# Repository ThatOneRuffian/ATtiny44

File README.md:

# ATtiny44
Messing with ATtiny44 MCU.

Making a multi-colored LED driver/controller.

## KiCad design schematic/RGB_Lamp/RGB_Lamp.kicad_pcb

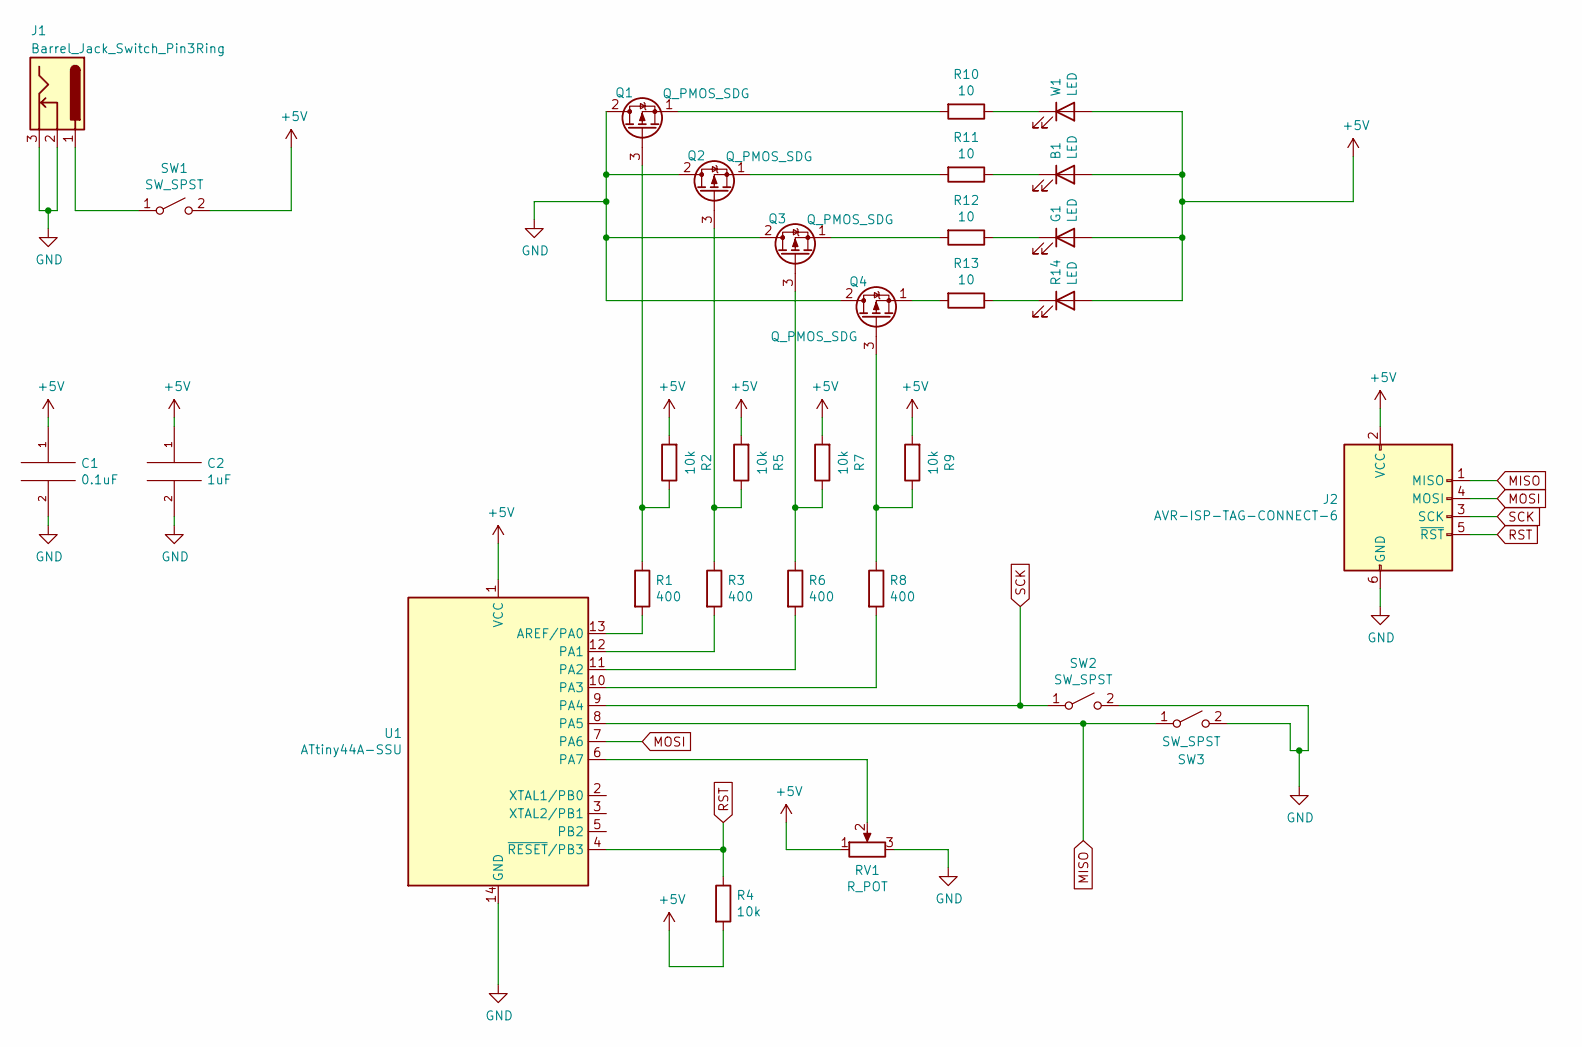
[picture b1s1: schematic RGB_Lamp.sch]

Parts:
B1: LED; PinHeader_1x02_P2.54mm_Vertical
C1: 0.1uF; C_Rect_L4.0mm_W2.5mm_P2.50mm
C2: 1uF; CP_Radial_D4.0mm_P1.50mm
G1: LED; PinHeader_1x02_P2.54mm_Vertical
J1: Barrel_Jack_Switch_Pin3Ring; BarrelJack_Horizontal
J2: AVR-ISP-TAG-CONNECT-6; TC2030-IDC-NL-10
Q1, Q2, Q3, Q4: Q_PMOS_SDG; SuperSOT-3
R1, R3, R6, R8: 400; R_Axial_DIN0207_L6.3mm_D2.5mm_P10.16mm_Horizontal
R2, R4, R5, R7, R9: 10k; R_Axial_DIN0207_L6.3mm_D2.5mm_P10.16mm_Horizontal
R10, R11, R12, R13: 10; R_Axial_DIN0207_L6.3mm_D2.5mm_P10.16mm_Horizontal
R14: LED; PinHeader_1x02_P2.54mm_Vertical
RV1: R_POT; Potentiometer_Omeg_PC16BU_Horizontal
SW1: SW_SPST; PinHeader_1x02_P2.54mm_Vertical
SW2, SW3: SW_SPST; SW_Tactile_SPST_Angled_PTS645Vx31-2LFS
U1: ATtiny44A-SSU; SOIC-14_3.9x8.7mm_P1.27mm
W1: LED; PinHeader_1x02_P2.54mm_Vertical

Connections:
+5V: B1.2 (A), C1.1, C2.1, G1.2 (A), J2.2 (VCC), R2.2, R4.2, R5.2, R7.2, R9.2, R14.2 (A), RV1.1, SW1.2 (B), U1.1 (VCC), W1.2 (A)
GND: C1.2, C2.2, J1.2, J1.3, J2.6 (GND), Q1.2 (D), Q2.2 (D), Q3.2 (D), Q4.2 (D), RV1.3, SW2.2 (B), SW3.2 (B), U1.14 (GND)
MISO: J2.1 (MISO), SW3.1 (A), U1.8 (PA5)
MOSI: J2.4 (MOSI), U1.7 (PA6)
unnamed: B1.1 (K), R11.1
unnamed: G1.1 (K), R12.1
unnamed: J1.1, SW1.1 (A)
unnamed: Q1.1 (S), R10.2
unnamed: Q1.3 (G), R1.1, R2.1
unnamed: Q2.1 (S), R11.2
unnamed: Q2.3 (G), R3.1, R5.1
unnamed: Q3.1 (S), R12.2
unnamed: Q3.3 (G), R6.1, R7.1
unnamed: Q4.1 (S), R13.2
unnamed: Q4.3 (G), R8.1, R9.1
unnamed: R1.2, U1.13 (AREF/PA0)
unnamed: R3.2, U1.12 (PA1)
unnamed: R6.2, U1.11 (PA2)
unnamed: R8.2, U1.10 (PA3)
unnamed: R10.1, W1.1 (K)
unnamed: R13.1, R14.1 (K)
unnamed: RV1.2, U1.6 (PA7)
RST: J2.5 (~RST), R4.1, U1.4 (~RESET~/PB3)
SCK: J2.3 (SCK), SW2.1 (A), U1.9 (PA4)

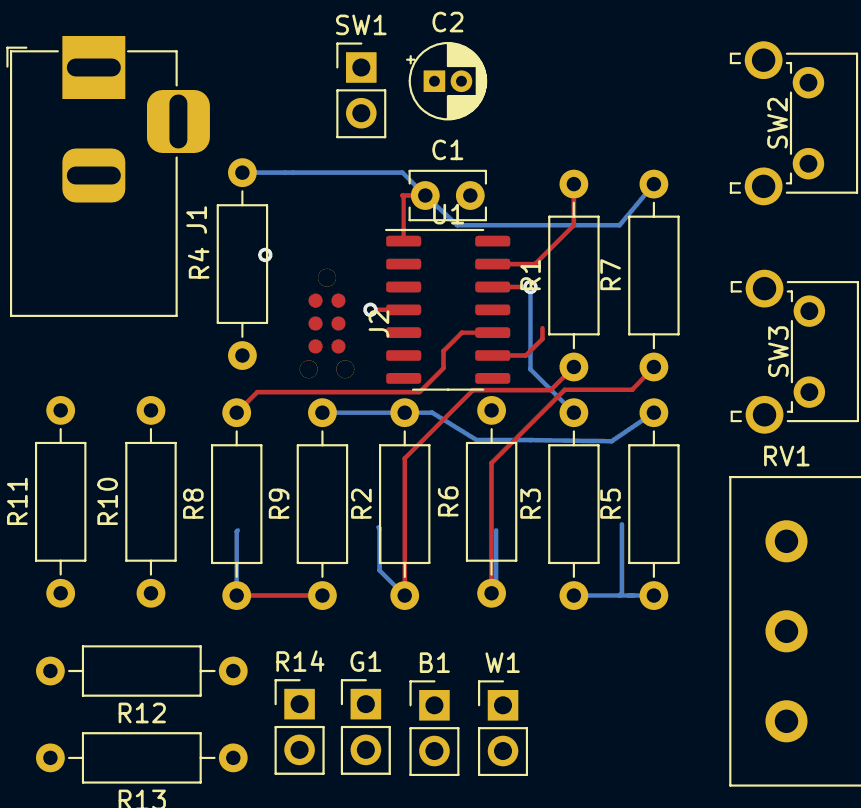
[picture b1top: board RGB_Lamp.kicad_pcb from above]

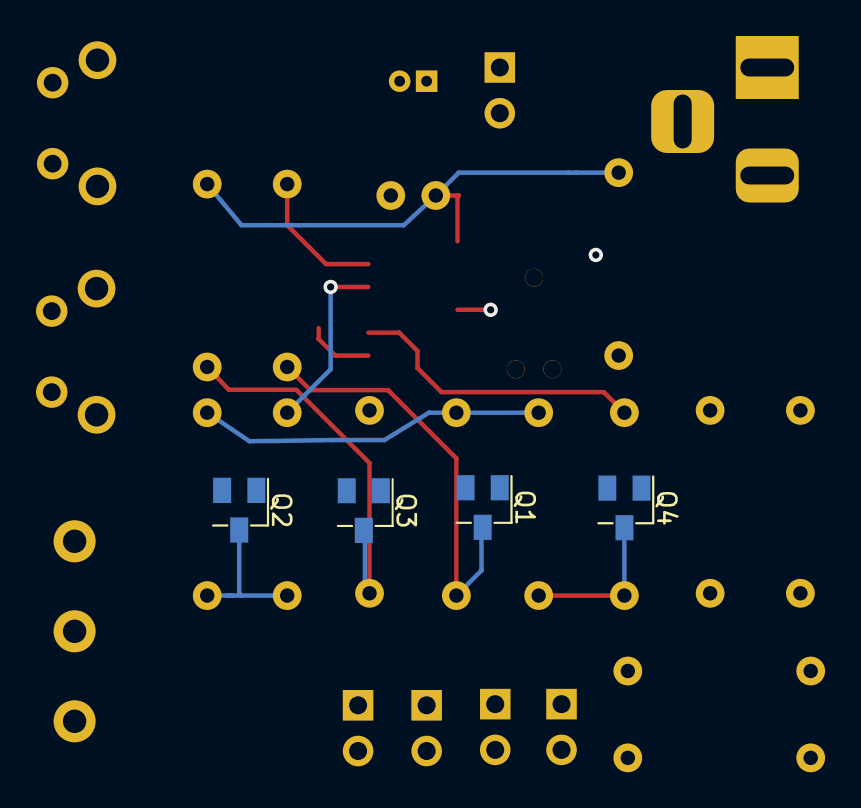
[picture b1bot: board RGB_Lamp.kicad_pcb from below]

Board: 2 copper layers, 30 parts (4 on the bottom side), 24 nets.

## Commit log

2021-02-24 Code cleanup
2021-02-25 Added delay function and cleanup
2021-02-25 Updated .gitignore
2021-02-25 Update README.md
    Updating README
2021-02-28 Finished software led functions
